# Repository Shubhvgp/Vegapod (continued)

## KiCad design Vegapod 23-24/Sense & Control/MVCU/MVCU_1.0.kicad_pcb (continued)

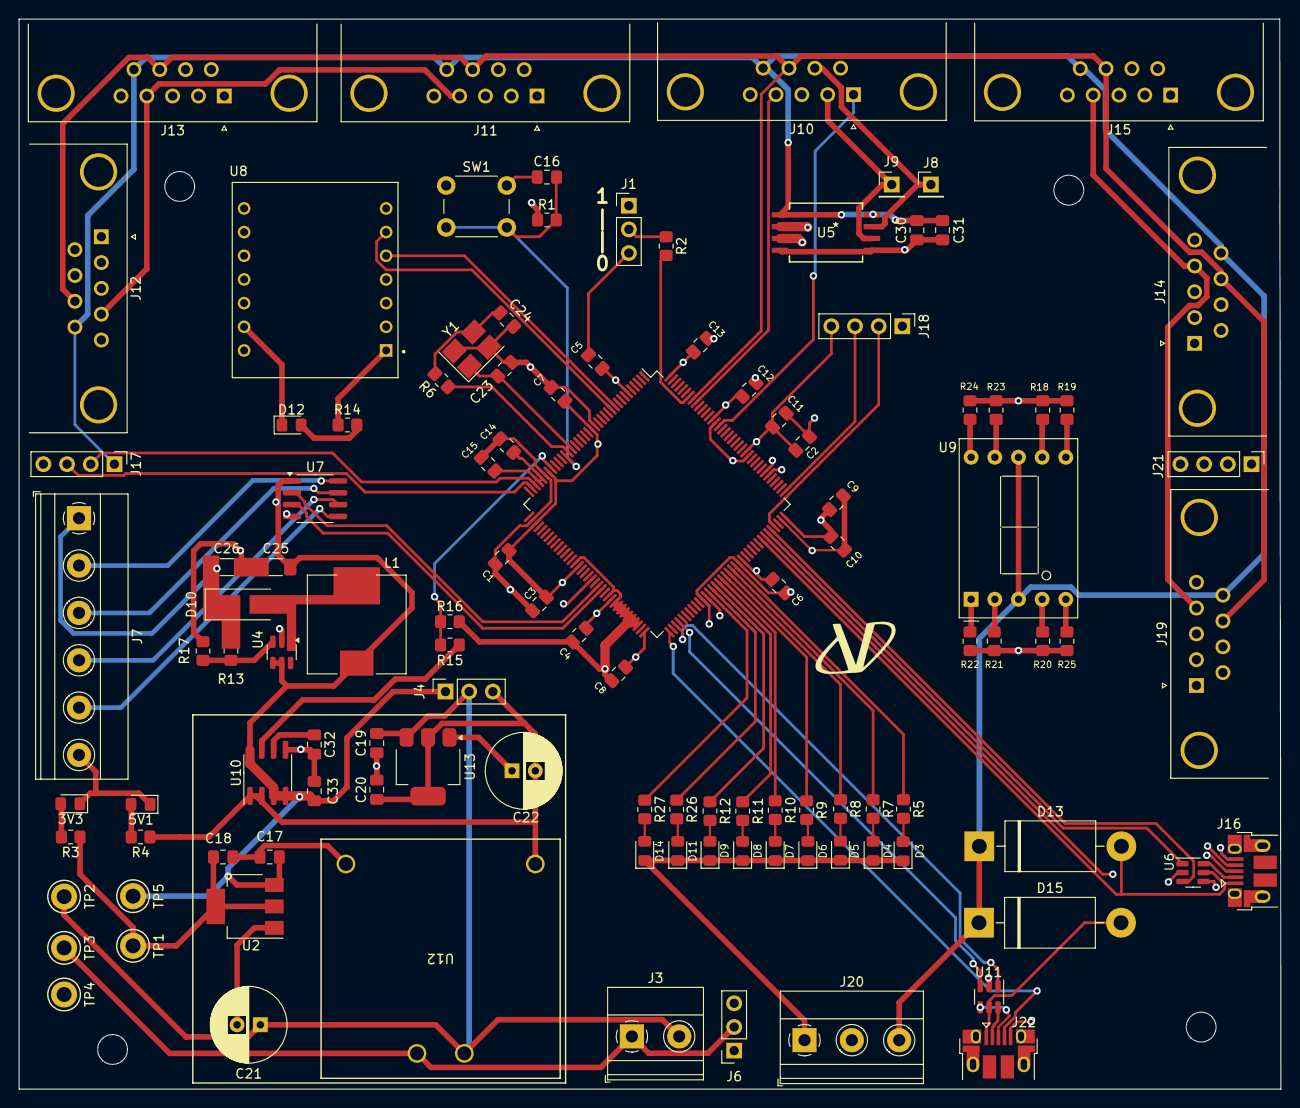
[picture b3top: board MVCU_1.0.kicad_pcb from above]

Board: 4 copper layers, 135.4 x 114.8 mm, 116 parts (0 on the bottom side), 81 nets.

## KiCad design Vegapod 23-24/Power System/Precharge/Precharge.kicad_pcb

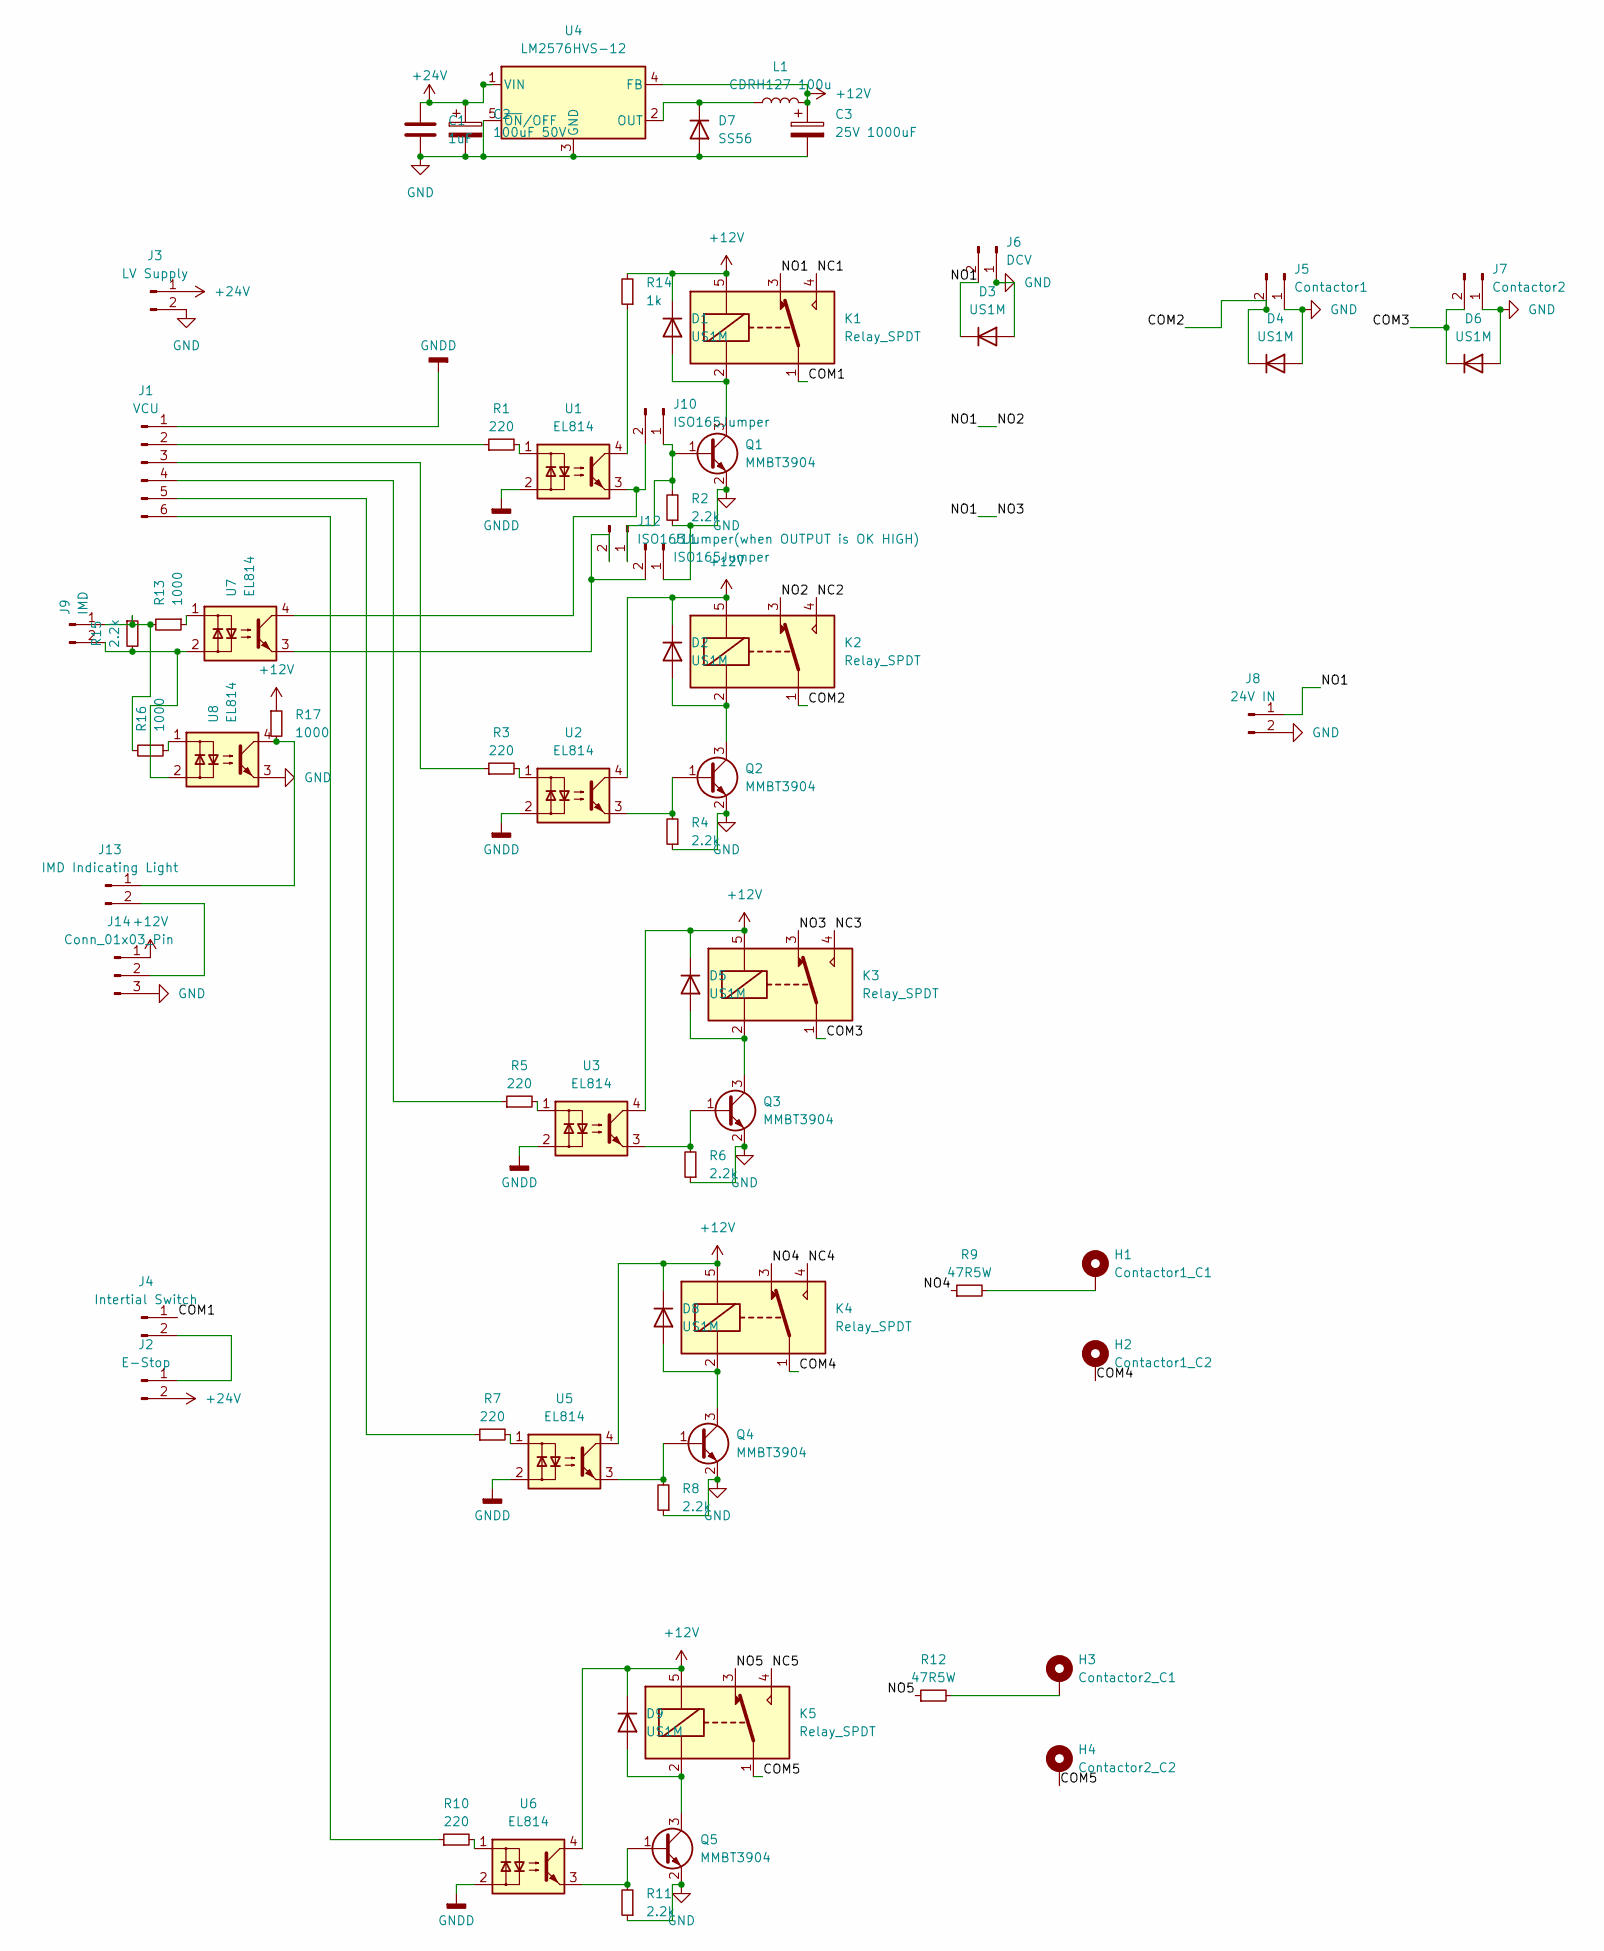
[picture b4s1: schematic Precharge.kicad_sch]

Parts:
C1: 1uF; C_1206_3216Metric_Pad1.33x1.80mm_HandSolder
C2: 100uF 50V; CP_Elec_8x10.5
C3: 25V 1000uF; CP_Elec_10x12.5
D1, D2, D3, D4, D5, D6, D8, D9: US1M; D_SMA-SMB_Universal_Handsoldering
D7: SS56; D_SMA-SMB_Universal_Handsoldering
H1: Contactor1_C1; MountingHole_6.4mm_M6_DIN965_Pad
H2: Contactor1_C2; MountingHole_6.4mm_M6_DIN965_Pad
H3: Contactor2_C1; MountingHole_6.4mm_M6_DIN965_Pad
H4: Contactor2_C2; MountingHole_6.4mm_M6_DIN965_Pad
J1: VCU; JST_XH_B6B-XH-A_1x06_P2.50mm_Vertical
J2: E-Stop; PhoenixContact_MCV_1,5_2-G-5.08_1x02_P5.08mm_Vertical
J3: LV Supply; PhoenixContact_MCV_1,5_2-G-5.08_1x02_P5.08mm_Vertical
J4: Intertial Switch; PhoenixContact_MCV_1,5_2-G-5.08_1x02_P5.08mm_Vertical
J5: Contactor1; PinHeader_1x02_P2.54mm_Vertical
J6: DCV; PhoenixContact_MCV_1,5_2-G-5.08_1x02_P5.08mm_Vertical
J7: Contactor2; PinHeader_1x02_P2.54mm_Vertical
J8: 24V IN; PinHeader_1x02_P2.54mm_Vertical
J9: IMD; PinHeader_1x02_P2.54mm_Vertical
J10, J11: ISO165Jumper; PinHeader_1x02_P1.27mm_Vertical
J12: ISO165Jumper(when OUTPUT is OK HIGH); PinHeader_1x02_P1.27mm_Vertical
J13: IMD Indicating Light; PhoenixContact_MCV_1,5_2-G-5.08_1x02_P5.08mm_Vertical
J14: Conn_01x03_Pin; PinHeader_1x03_P1.27mm_Vertical
K1, K2, K3, K4, K5: Relay_SPDT; Relay_SPDT_Omron-G5LE-1
L1: CDRH127 100u; L_12x12mm_H8mm
Q1, Q2, Q3, Q4, Q5: MMBT3904; SOT-23_Handsoldering
R1, R3, R5, R7, R10: 220; R_0805_2012Metric_Pad1.20x1.40mm_HandSolder
R2, R4, R6, R8, R11, R15: 2.2k; R_0805_2012Metric_Pad1.20x1.40mm_HandSolder
R9, R12: 47R5W; R_Axial_DIN0617_L17.0mm_D6.0mm_P7.62mm_Vertical
R13, R16, R17: 1000; R_0805_2012Metric_Pad1.20x1.40mm_HandSolder
R14: 1k; R_0805_2012Metric_Pad1.20x1.40mm_HandSolder
U1, U2, U3, U5, U6, U7, U8: EL814; SMDIP-4_W9.53mm
U4: LM2576HVS-12; TO-263-5_TabPin3

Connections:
+12V: C3.1, D1.1 (K), D2.1 (K), D5.1 (K), D8.1 (K), D9.1 (K), J14.1, K1.5, K2.5, K3.5, K4.5, K5.5, L1.2, R14.2, R17.1, U2.4, U3.4, U4.4 (FB), U5.4, U6.4
+24V: C1.1, C2.1, J2.2, J3.1, U4.1 (VIN)
/COM1: J4.1, K1.1
/COM2: D4.1 (K), J5.2, K2.1
/COM3: D6.1 (K), J7.2, K3.1
/COM4: H2.1, K4.1
/COM5: H4.1, K5.1
/NC1: K1.4
/NC2: K2.4
/NC3: K3.4
/NC4: K4.4
/NC5: K5.4
/NO1: D3.1 (K), J6.2, J8.1, K1.3, K2.3, K3.3
/NO4: K4.3, R9.1
/NO5: K5.3, R12.1
GND: C1.2, C2.2, C3.2, D3.2 (A), D4.2 (A), D6.2 (A), D7.2 (A), J3.2, J5.1, J6.1, J7.1, J8.2, J11.1, J14.3, Q1.2 (E), Q2.2 (E), Q3.2 (E), Q4.2 (E), Q5.2 (E), R2.1, R4.1, R6.1, R8.1, R11.1, U4.3 (GND), U4.5 (~ON/OFF), U8.3
GNDD: J1.1, U1.2, U2.2, U3.2, U5.2, U6.2
unnamed: D1.2 (A), K1.2, Q1.3 (C)
unnamed: D2.2 (A), K2.2, Q2.3 (C)
unnamed: D5.2 (A), K3.2, Q3.3 (C)
unnamed: D7.1 (K), L1.1, U4.2 (OUT)
unnamed: D8.2 (A), K4.2, Q4.3 (C)
unnamed: D9.2 (A), K5.2, Q5.3 (C)
unnamed: H1.1, R9.2
unnamed: H3.1, R12.2
unnamed: J1.2, R1.1
unnamed: J1.3, R3.1
unnamed: J1.4, R5.1
unnamed: J1.5, R7.1
unnamed: J1.6, R10.1
unnamed: J2.1, J4.2
unnamed: J9.1, R13.2, R15.1, R16.2
unnamed: J9.2, R15.2, U7.2, U8.2
unnamed: J10.1, J12.1, Q1.1 (B), R2.2
unnamed: J10.2, U1.3, U7.4
unnamed: J11.2, J12.2, U7.3
unnamed: J13.1, R17.2, U8.4
unnamed: J13.2, J14.2
unnamed: Q2.1 (B), R4.2, U2.3
unnamed: Q3.1 (B), R6.2, U3.3
unnamed: Q4.1 (B), R8.2, U5.3
unnamed: Q5.1 (B), R11.2, U6.3
unnamed: R1.2, U1.1
unnamed: R3.2, U2.1
unnamed: R5.2, U3.1
unnamed: R7.2, U5.1
unnamed: R10.2, U6.1
unnamed: R13.1, U7.1
unnamed: R14.1, U1.4
unnamed: R16.1, U8.1

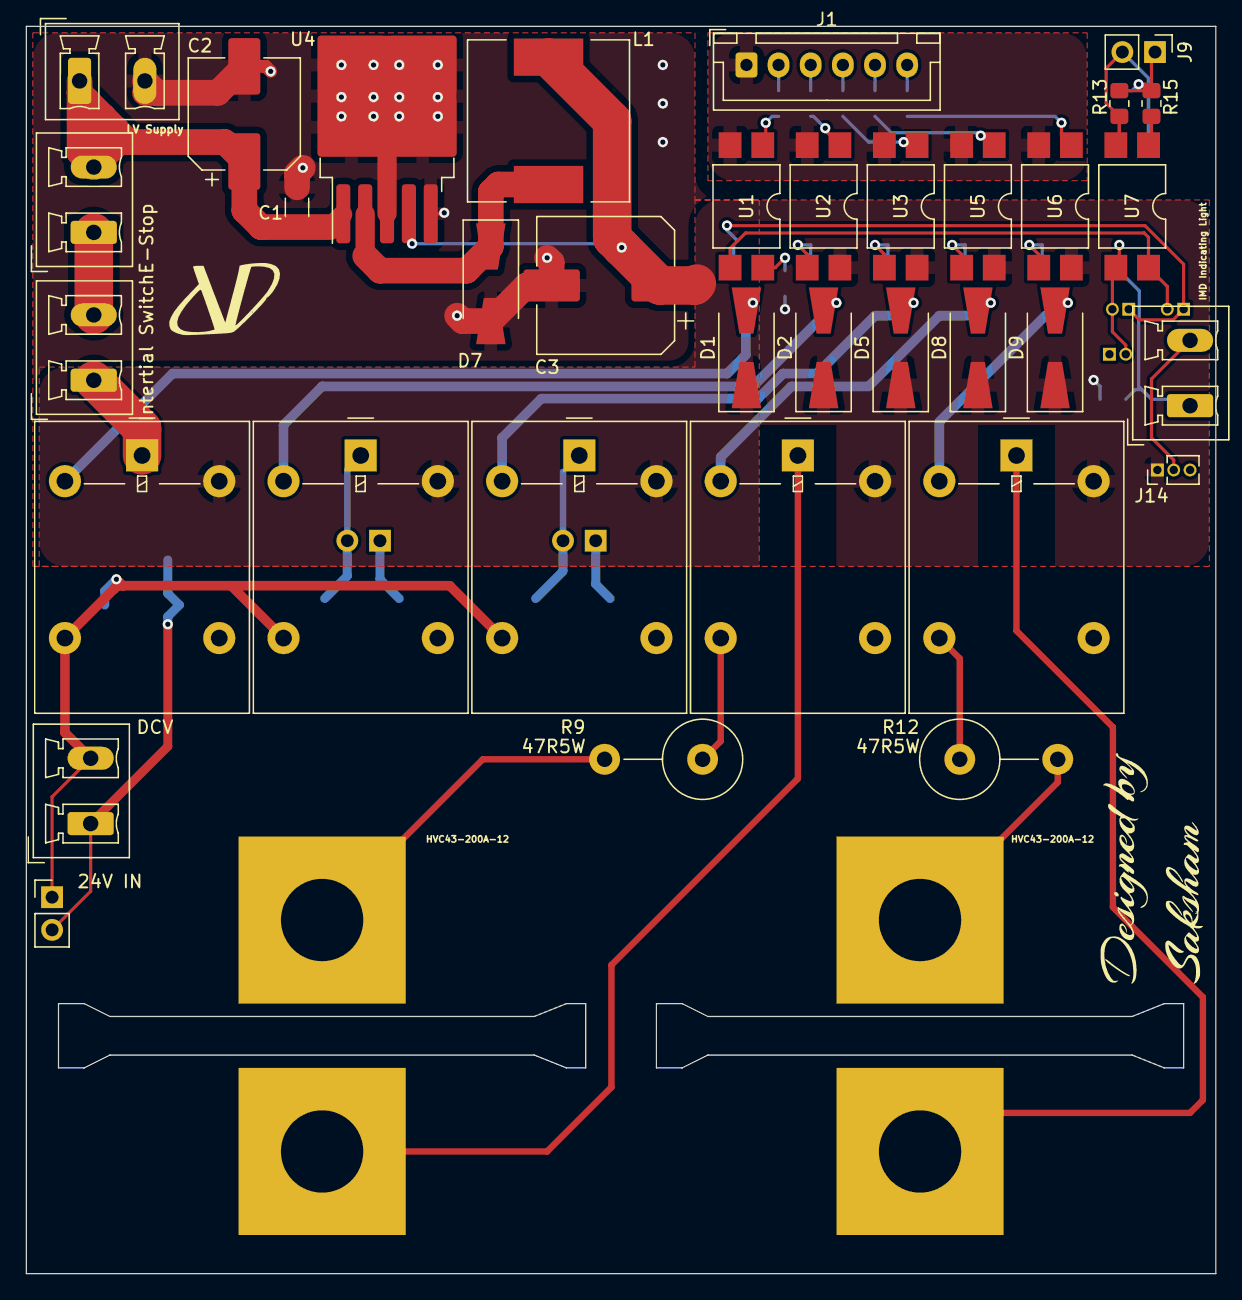
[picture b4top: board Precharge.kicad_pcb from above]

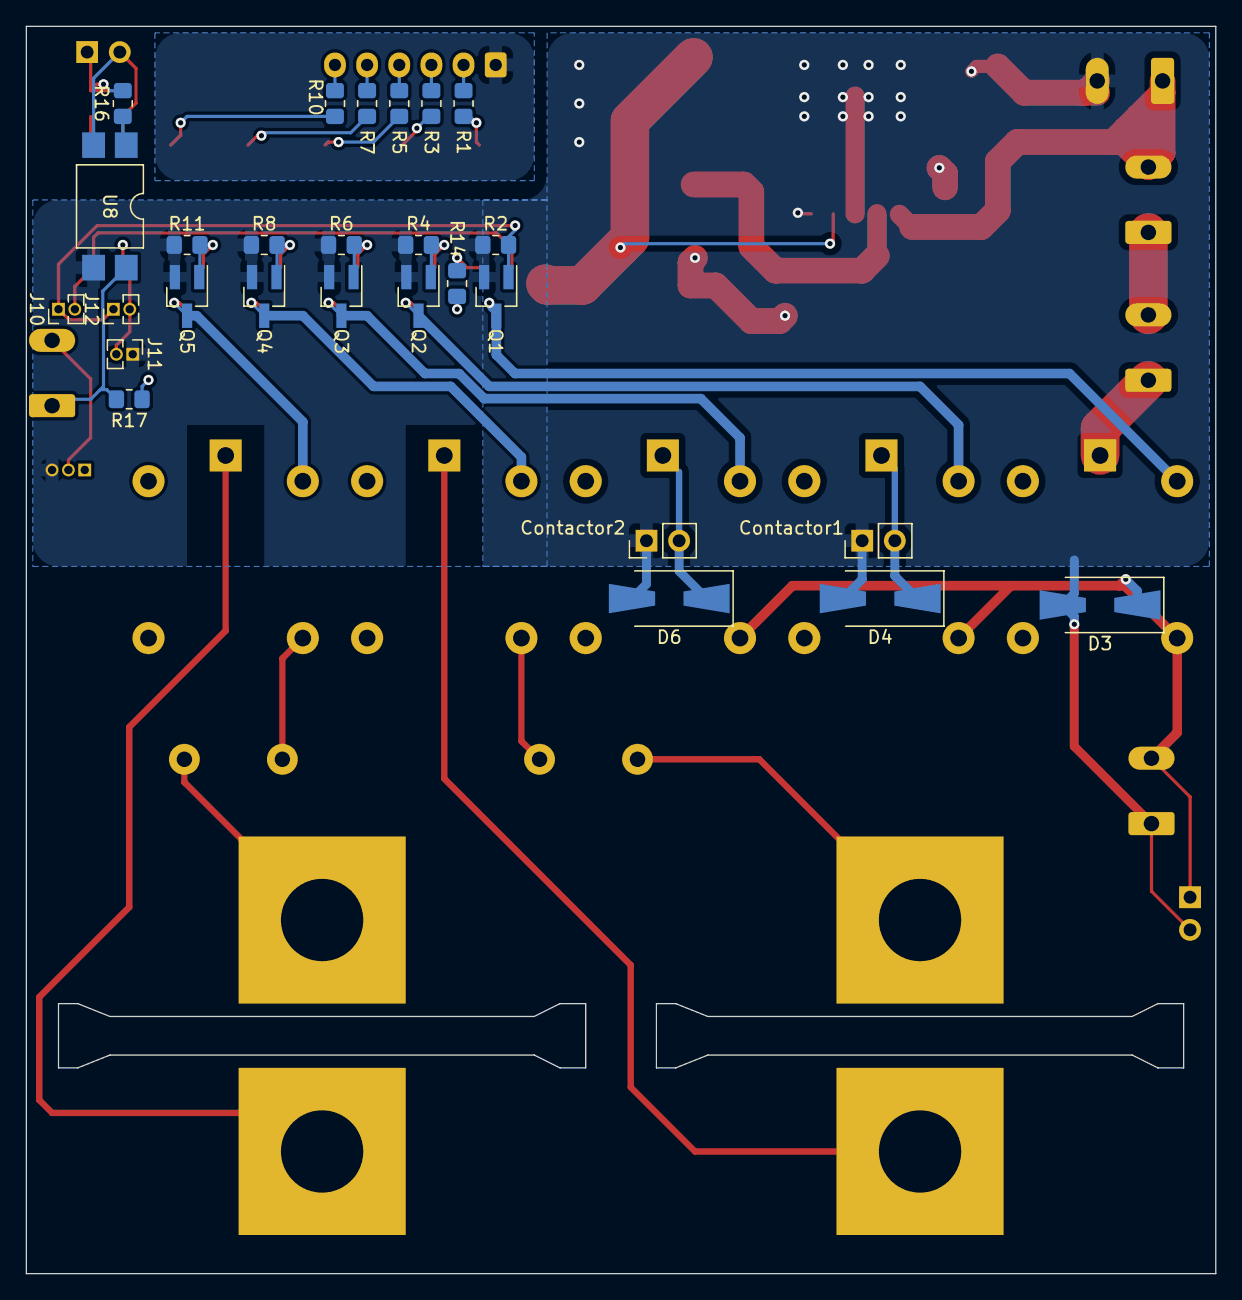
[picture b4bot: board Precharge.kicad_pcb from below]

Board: 2 copper layers, 92.5 x 97.0 mm, 66 parts (27 on the bottom side), 45 nets.
